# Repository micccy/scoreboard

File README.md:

# Mictronic5677 scoreboard, a basic electronic scoreboard project

**Standard disclaimer:** _this is some project of mine that was created to tackle some very specific need and might not work as well elsewhere. However, it may still be useful to someone, so here it is._

**Description:** The mictronic5677 scoreboard project was born as a way to revive an old broken rusty electronic scoreboard chassis we found laying around. All of the control circuitry has been redone from scratch, it now implements an ATmega328P running at 4MHz and programmed in assembler to ensure exact timings. Every development choice has been taken as a direct response to precise needs, to ensure max reliability and most importantly to keep it cheap and made from easy to source components. A time signal radio receiver has been added to keep the time-of-day clock accurate 

**Status:** _Kinda functional (basic operation only)- incomplete documentation (no schematics available yet)_

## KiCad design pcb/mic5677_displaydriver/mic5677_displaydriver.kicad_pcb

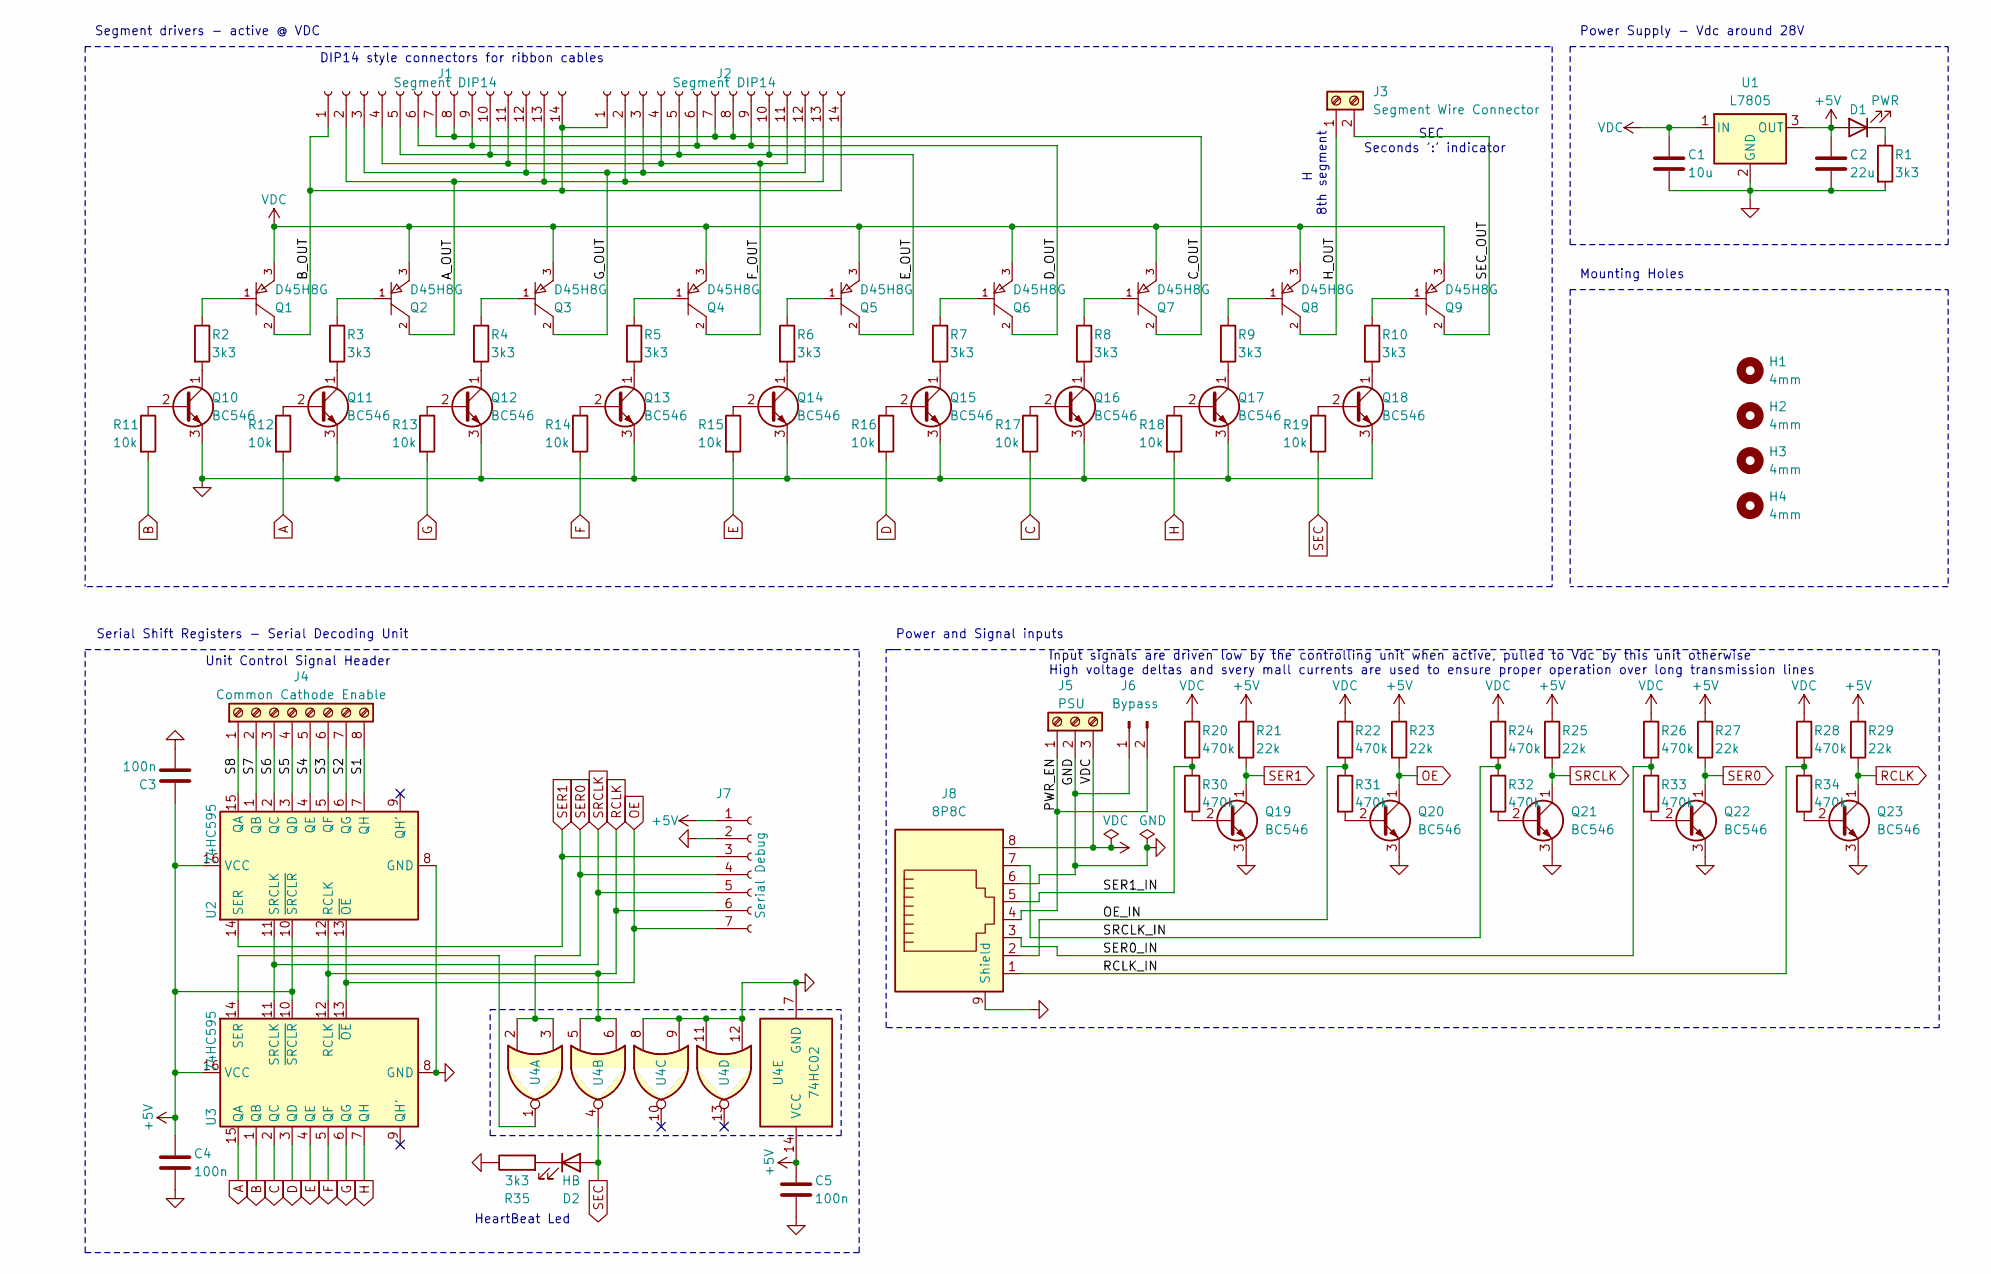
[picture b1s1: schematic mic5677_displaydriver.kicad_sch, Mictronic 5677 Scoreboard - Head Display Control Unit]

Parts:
C1: 10u; C_Disc_D3.8mm_W2.6mm_P2.50mm
C2: 22u; C_Disc_D3.8mm_W2.6mm_P2.50mm
C3, C4, C5: 100n; C_Disc_D3.8mm_W2.6mm_P2.50mm
D1: PWR; LED_D3.0mm
D2: HB; LED_D3.0mm
H1, H2, H3, H4: 4mm; MountingHole_4mm
J1, J2: Segment DIP14; DIP-14_W7.62mm_Socket
J3: Segment Wire Connector; TerminalBlock_bornier-2_P5.08mm
J4: Common Cathode Enable; TerminalBlock_RND_205-00238_1x08_P5.08mm_Horizontal
J5: PSU; TerminalBlock_bornier-3_P5.08mm
J6: Bypass; PinHeader_1x02_P2.54mm_Vertical
J7: Serial Debug; PinSocket_1x07_P2.54mm_Vertical
J8: 8P8C; RJ45_Amphenol_54602-x08_Horizontal
Q1, Q2, Q3, Q4, Q5, Q6, Q7, Q8, Q9: D45H8G; On_Semiconductor-D45H8G-Manufacturer_Recommended
Q10, Q11, Q12, Q13, Q14, Q15, Q16, Q17, Q18, Q19, Q20, Q21, Q22, Q23: BC546; TO-92_Inline
R1, R2, R3, R4, R5, R6, R7, R8, R9, R10, R35: 3k3; R_Axial_DIN0204_L3.6mm_D1.6mm_P7.62mm_Horizontal
R11, R12, R13, R14, R15, R16, R17, R18, R19: 10k; R_Axial_DIN0204_L3.6mm_D1.6mm_P7.62mm_Horizontal
R20, R22, R24, R26, R28, R30, R31, R32, R33, R34: 470k; R_Axial_DIN0204_L3.6mm_D1.6mm_P7.62mm_Horizontal
R21, R23, R25, R27, R29: 22k; R_Axial_DIN0204_L3.6mm_D1.6mm_P7.62mm_Horizontal
U1: L7805; TO-220-3_Vertical
U2, U3: 74HC595; DIP-16_W7.62mm_Socket
U4: 74HC02; DIP-14_W7.62mm_Socket

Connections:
+5V: C2.1, C3.1, C4.1, C5.1, D1.2 (A), J7.1, R21.1, R23.1, R25.1, R27.1, R29.1, U1.3 (OUT), U2.10 (~SRCLR), U2.16 (VCC), U3.10 (~SRCLR), U3.16 (VCC), U4.14 (VCC)
/A_OUT: J1.2, J1.13, J2.2, J2.13, Q2.2 (C)
/B_OUT: J1.1, J1.14, J2.1, J2.14, Q1.2 (C)
/C_OUT: J1.7, J1.8, J2.7, J2.8, Q7.2 (C)
/D_OUT: J1.6, J1.9, J2.6, J2.9, Q6.2 (C)
/E_OUT: J1.5, J1.10, J2.5, J2.10, Q5.2 (C)
/F_OUT: J1.4, J1.11, J2.4, J2.11, Q4.2 (C)
/G_OUT: J1.3, J1.12, J2.3, J2.12, Q3.2 (C)
/H_OUT: J3.1, Q8.2 (C)
/OE_IN: J8.2, R22.2, R31.1
/PWR_EN: J5.1, J6.2, J8.4
/RCLK_IN: J8.1, R28.2, R34.1
/S1: J4.8, U2.7 (QH)
/S2: J4.7, U2.6 (QG)
/S3: J4.6, U2.5 (QF)
/S4: J4.5, U2.4 (QE)
/S5: J4.4, U2.3 (QD)
/S6: J4.3, U2.2 (QC)
/S7: J4.2, U2.1 (QB)
/S8: J4.1, U2.15 (QA)
/SEC_OUT: J3.2, Q9.2 (C)
/SER0_IN: J8.3, R26.2, R33.1
/SER1_IN: J8.5, R20.2, R30.1
/SRCLK_IN: J8.7, R24.2, R32.1
A: R12.2, U3.15 (QA)
B: R11.2, U3.1 (QB)
C: R17.2, U3.2 (QC)
D: R16.2, U3.3 (QD)
E: R15.2, U3.4 (QE)
F: R14.2, U3.5 (QF)
G: R13.2, U3.6 (QG)
GND: C1.2, C2.2, C3.2, C4.2, C5.2, J5.2, J6.1, J7.2, J8.6, J8.9 (Shield), Q10.3 (E), Q11.3 (E), Q12.3 (E), Q13.3 (E), Q14.3 (E), Q15.3 (E), Q16.3 (E), Q17.3 (E), Q18.3 (E), Q19.3 (E), Q20.3 (E), Q21.3 (E), Q22.3 (E), Q23.3 (E), R1.2, R35.1, U1.2 (GND), U2.8 (GND), U3.8 (GND), U4.7 (GND), U4.8, U4.9, U4.11, U4.12
H: R18.2, U3.7 (QH)
unnamed: D1.1 (K), R1.1
unnamed: D2.1 (K), R35.2
unnamed: Q1.1 (B), R2.1
unnamed: Q2.1 (B), R3.1
unnamed: Q3.1 (B), R4.1
unnamed: Q4.1 (B), R5.1
unnamed: Q5.1 (B), R6.1
unnamed: Q6.1 (B), R7.1
unnamed: Q7.1 (B), R8.1
unnamed: Q8.1 (B), R9.1
unnamed: Q9.1 (B), R10.1
unnamed: Q10.2 (B), R11.1
unnamed: Q10.1 (C), R2.2
unnamed: Q11.2 (B), R12.1
unnamed: Q11.1 (C), R3.2
unnamed: Q12.2 (B), R13.1
unnamed: Q12.1 (C), R4.2
unnamed: Q13.2 (B), R14.1
unnamed: Q13.1 (C), R5.2
unnamed: Q14.2 (B), R15.1
unnamed: Q14.1 (C), R6.2
unnamed: Q15.2 (B), R16.1
unnamed: Q15.1 (C), R7.2
unnamed: Q16.2 (B), R17.1
unnamed: Q16.1 (C), R8.2
unnamed: Q17.2 (B), R18.1
unnamed: Q17.1 (C), R9.2
unnamed: Q18.2 (B), R19.1
unnamed: Q18.1 (C), R10.2
unnamed: Q19.2 (B), R30.2
unnamed: Q20.2 (B), R31.2
unnamed: Q21.2 (B), R32.2
unnamed: Q22.2 (B), R33.2
unnamed: Q23.2 (B), R34.2
unnamed: U3.14 (SER), U4.1
OE: J7.7, Q20.1 (C), R23.2, U2.13 (~OE), U3.13 (~OE)
RCLK: J7.6, Q23.1 (C), R29.2, U2.12 (RCLK), U3.12 (RCLK), U4.5, U4.6
SEC: D2.2 (A), R19.2, U4.4
SER0: J7.4, Q22.1 (C), R27.2, U4.2, U4.3
SER1: J7.3, Q19.1 (C), R21.2, U2.14 (SER)
SRCLK: J7.5, Q21.1 (C), R25.2, U2.11 (SRCLK), U3.11 (SRCLK)
VDC: C1.1, J5.3, J8.8, Q1.3 (E), Q2.3 (E), Q3.3 (E), Q4.3 (E), Q5.3 (E), Q6.3 (E), Q7.3 (E), Q8.3 (E), Q9.3 (E), R20.1, R22.1, R24.1, R26.1, R28.1, U1.1 (IN)

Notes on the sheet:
Unit Control Signal Header
H 8th segment
Power and Signal inputs
Input signals are driven low by the controlling unit when active, pulled to Vdc by this unit otherwise High voltage deltas and svery mall currents are used to ensure proper operation over long transmission lines
SEC Seconds ':' indicator
DIP14 style connectors for ribbon cables
Mounting Holes
Serial Shift Registers - Serial Decoding Unit
Segment drivers - active @ VDC
Power Supply - Vdc around 28V
HeartBeat Led

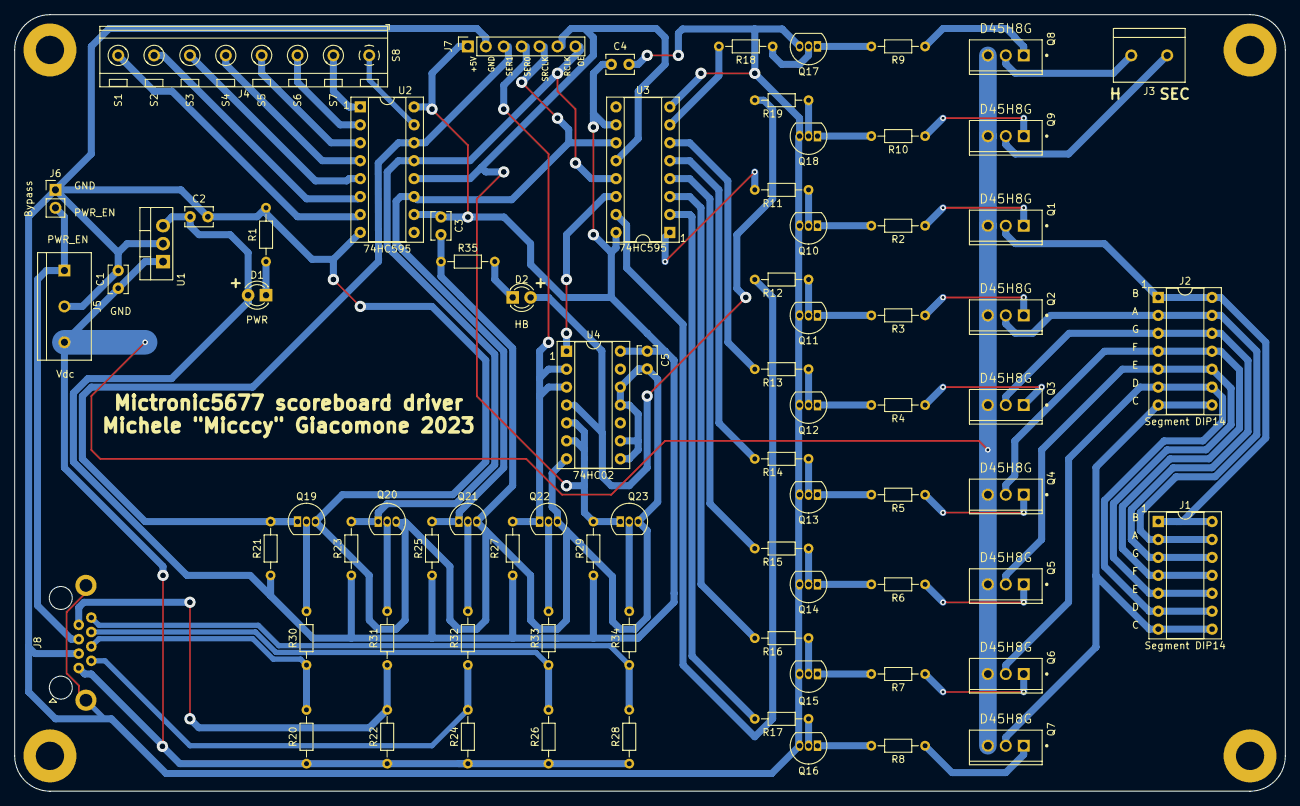
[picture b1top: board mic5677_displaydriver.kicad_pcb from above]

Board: 2 copper layers, 180.0 x 110.0 mm, 81 parts (0 on the bottom side), 75 nets.

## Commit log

2023-06-22 Development moved to github
2023-06-22 Some translations
2023-06-23 Added watchdog support and power reduction
2023-06-23 Added translations
2023-06-24 Added (some) documentation
2023-06-24 Changed scource code structure
2023-06-24 Moved some operations out of main
2023-06-24 Fixed opF-2 format and translations
2023-06-24 moved op3-4 out of main
2023-06-26 moved op5-6 out of main
2023-06-26 Fixed bad operation identifiers
2023-06-27 Added boot display test pattern
2023-06-27 Added operation descriptive filenames
2023-06-28 Fixed opF boot display test pattern
2023-06-28 Minor fixes, op9 pulled out of main and simplified
2023-06-28 Fixed opF addressing
2023-07-07 added display driver pcb project
2023-07-07 Added some component documentation
2023-07-08 Updated display pcb
2023-07-09 Improved display driver pcb
2023-07-10 Finished display driver pcb
2023-07-10 Added some silkscreen on pcb and changed io style
2023-07-11 Made display driver pcb slightly worse but easier to manufacture
2023-07-13 Added back fill zones to display driver pcb
2023-07-13 Added back printable file
2023-07-13 Small dir struct changes
2023-07-13 Other small dir struct changes
2023-07-13 Removed ignored dirs
2023-07-13 Made display driver pcb work both with and without filled fill zones
2023-07-13 MadeAdded gnd pads to port on d.driver pcb
2023-07-13 Made ddriver pcb project pretty
2023-07-13 Added ddriver front printable document
2023-07-16 Added power pins on serial debug port
2023-07-17 Updated ddriver to v2.3
2023-07-17 Rotated pdfs
2023-07-17 fixed ddriver front pdf
2023-07-17 Changed segment bitmaps
2023-07-18 Renamed doc files
2023-07-19 Moved ddriver HB led, adopted better 8p8c pinout, improved fill zones
